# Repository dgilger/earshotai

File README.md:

# Earshot

A self-hosted, DIY AI note taker. Earshot records conversations, turns them into text on hardware you own,
and keeps the audio away from third-party clouds.

> **Recording consent:** laws differ by country and state. Some places require every person's consent
> before you record a conversation. Check the law where you use Earshot.

## Parts of the project

| Folder | What it is | Status |
|---|---|---|
| [`android/`](android/README.md) | Android app: record, transcribe on the phone with speaker labels, save each transcript as a `.txt` file in a folder you choose. Audio is deleted after. | Works; APK built by GitHub Actions |
| [`server/`](server/) | Python service: receives audio over HTTP, transcribes with faster-whisper, optional summary (Claude API or any OpenAI-compatible local LLM). | Desk prototype |
| [`firmware/`](firmware/) | PlatformIO firmware for an ESP32-S3 board (ES8311 codec mic, touchscreen): record and upload to the server. | Desk prototype |
| [`hardware/`](hardware/SPEC.md) | Wearable rev A: nRF52840 board in KiCad 9, with JLCPCB fab files, plus a sealed 3D-printable enclosure (CadQuery). | Designed, not built |

## Quick start

**Android app.** Open the **Actions** tab, select the latest **Android APK** run, download `earshot-apk`,
and install the APK on an arm64 Android 10+ phone. See [`android/README.md`](android/README.md).

**Server.**
```sh
cd server
uv venv --python 3.12 .venv
uv pip install --python .venv/bin/python -r requirements.txt
cp .env.example .env        # choose a summary backend, or SUMMARY_BACKEND=none
.venv/bin/python -u earshot_server.py   # listens on port 8000
```

**Self-hosted server.** Install, web portal, remote access and setup details are in
[`server/README.md`](server/README.md).

**Firmware.** Copy `firmware/include/secrets.example.h` to `secrets.h`, fill in your Wi-Fi and server URL,
then run `pio run -t upload` from `firmware/`.

## Privacy

- The Android app transcribes on the phone. No audio or text leaves the phone except through the folder you pick.
- The server runs on your own machine. Summaries go to the Claude API only if you select that backend;
  select `local` or `none` to keep everything on your network.
- Secrets (`secrets.h`, `.env`) are gitignored. Do not commit them.

## License

MIT, see [LICENSE](LICENSE). Some files keep their own licenses:
- `android/app/src/main/java/com/k2fsa/sherpa/onnx/`: from [sherpa-onnx](https://github.com/k2-fsa/sherpa-onnx), Apache-2.0.
- `android/app/src/main/res/font/`: Silkscreen and Space Mono, SIL Open Font License (see `android/licenses/`).
- `hardware/earshot-revA/lib/`: footprints and 3D models imported from LCSC/EasyEDA with easyeda2kicad.

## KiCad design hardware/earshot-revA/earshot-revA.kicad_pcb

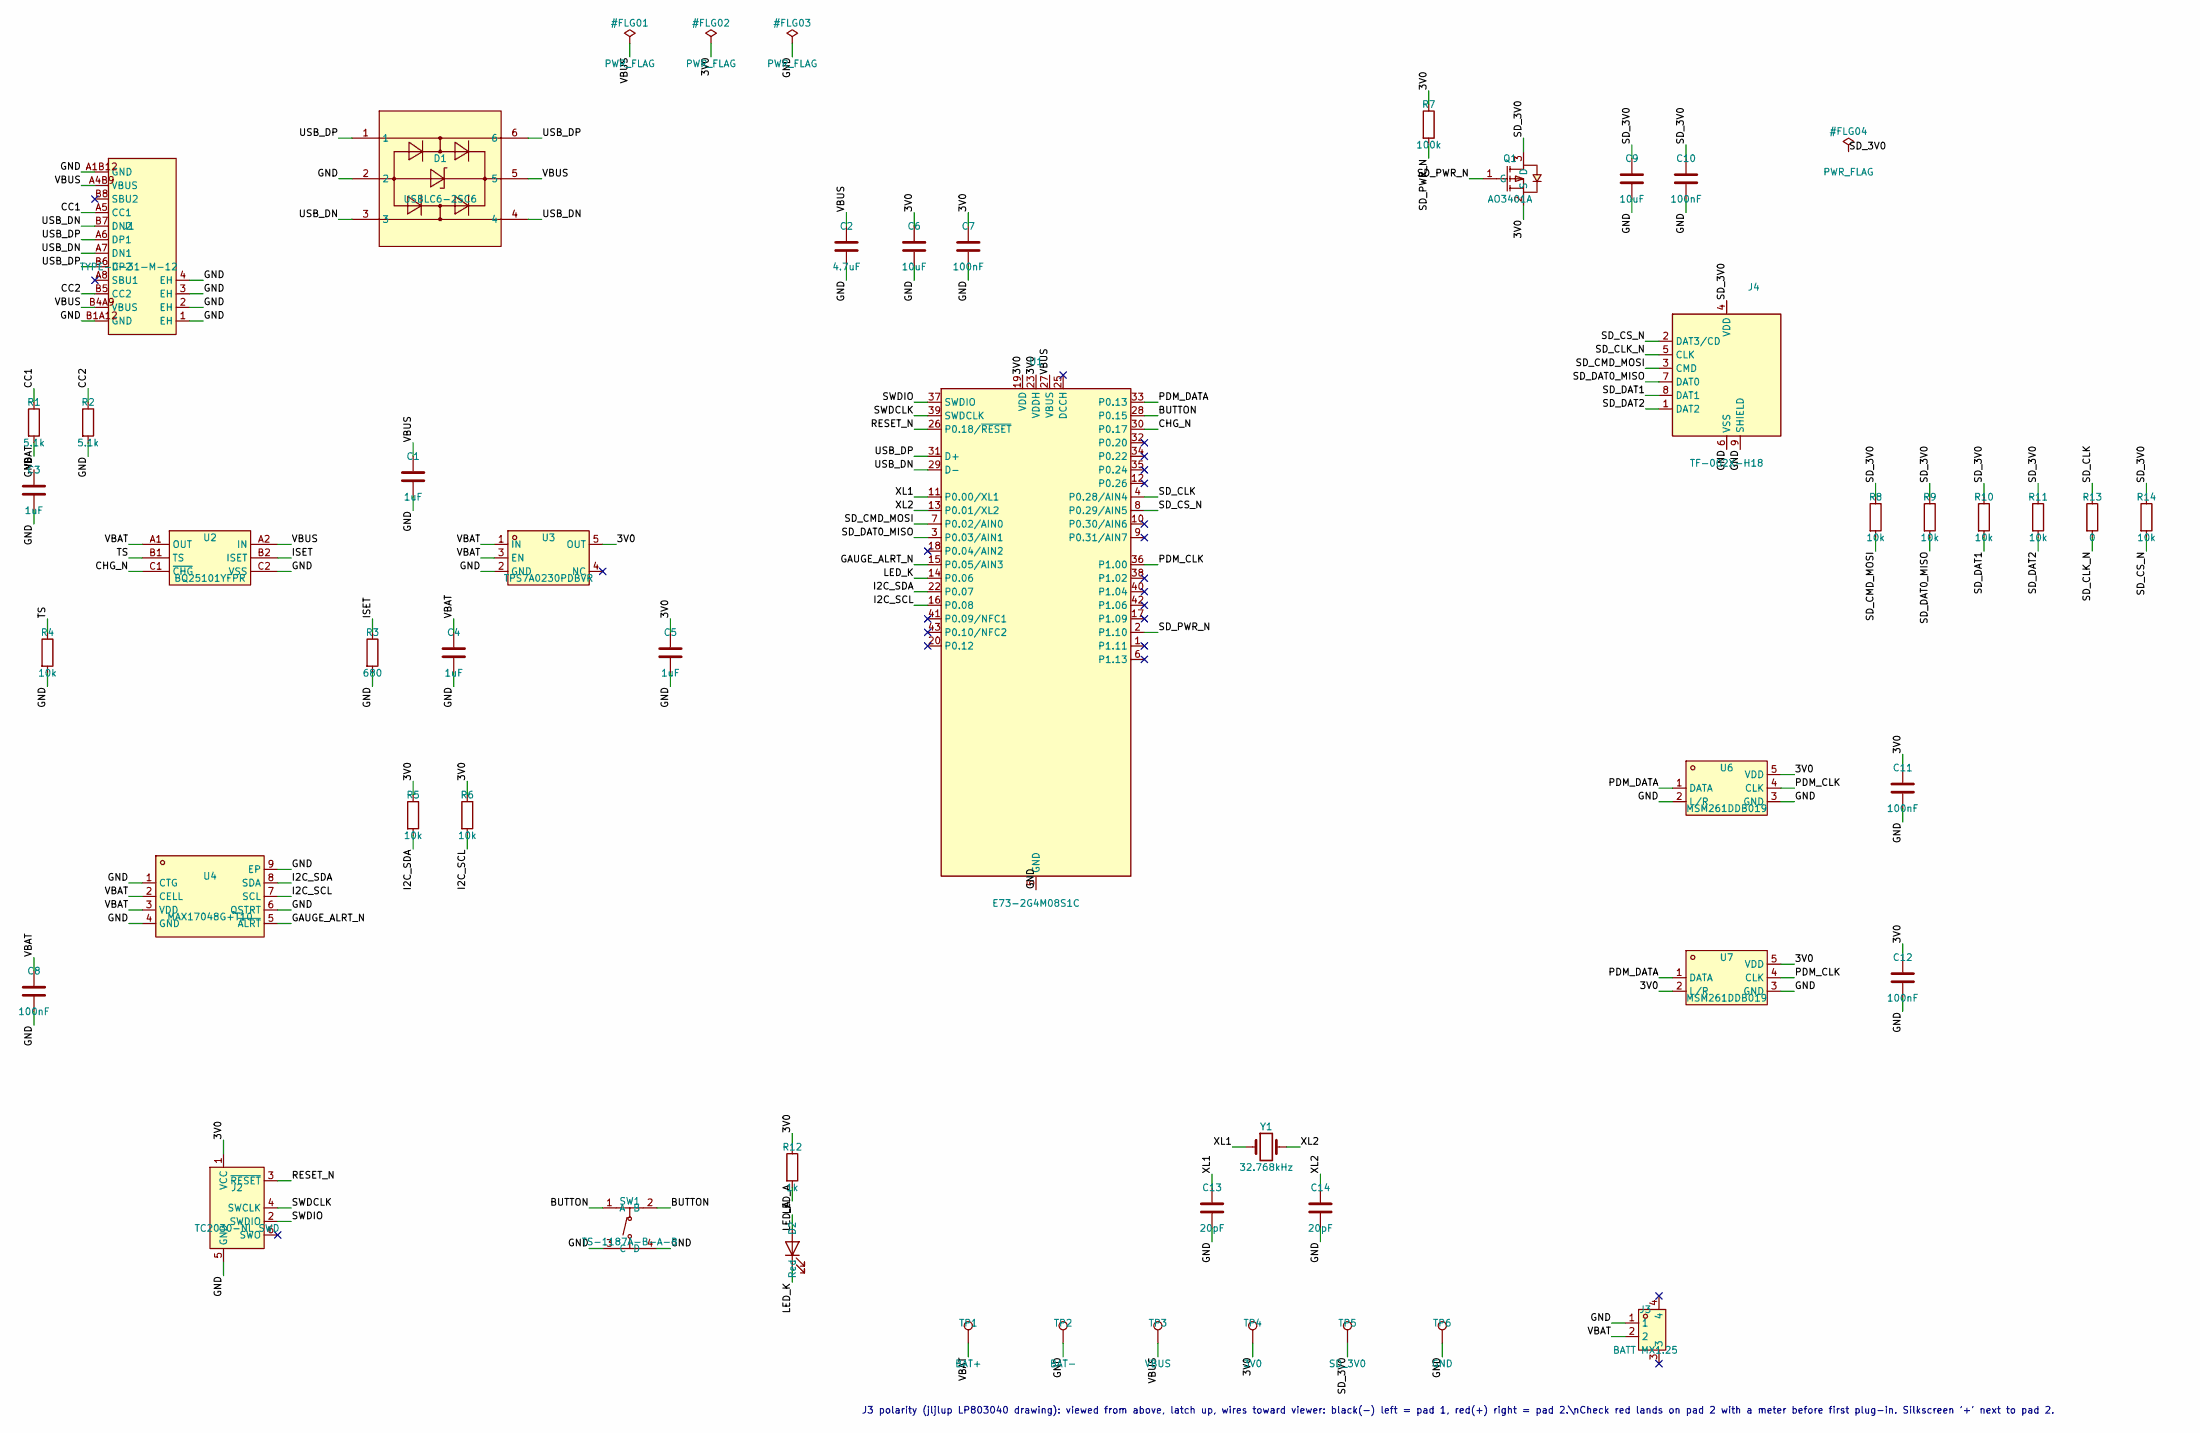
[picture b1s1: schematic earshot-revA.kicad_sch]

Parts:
C1, C3, C4, C5: 1uF; C_0402_1005Metric; LCSC Part C52923
C2: 4.7uF; C_0603_1608Metric; LCSC Part C19666
C6, C9: 10uF; C_0603_1608Metric; LCSC Part C19702
C7, C8, C10, C11, C12: 100nF; C_0402_1005Metric; LCSC Part C1525
C13, C14: 20pF; C_0402_1005Metric; LCSC Part C1554
D1: USBLC6-2SC6; SOT-23-6_L2.9-W1.6-P0.95-LS2.8-BL
D2: Red; LED_0603_1608Metric; LCSC C2286
J1: TYPE-C-31-M-12; USB-C_SMD-TYPE-C-31-M-12_1
J2: TC2030-NL SWD; Tag-Connect_TC2030-IDC-NL_2x03_P1.27mm_Vertical
J3: BATT MX1.25; CONN-SMD_2P-P1.25-2
J4: TF-002X-H18; microSD_Hinged_SOFNG_TF-002X-H18; MPN TF-002X-H18; LCSC Part C125814
Q1: AO3401A; SOT-23_L2.9-W1.3-P1.90-LS2.4-BR
R1, R2: 5.1k; R_0402_1005Metric; LCSC Part C25905
R3: 680; R_0402_1005Metric; LCSC Part C25130
R4, R5, R6, R8, R9, R10, R11, R14: 10k; R_0402_1005Metric; LCSC Part C60490
R7: 100k; R_0402_1005Metric; LCSC Part C25741
R12: 1k; R_0402_1005Metric; LCSC Part C11702
R13: 0; R_0402_1005Metric; LCSC Part C17168
SW1: TS-1187A-B-A-B; SW-SMD_4P-L5.1-W5.1-P3.70-LS6.5-TL_H1.5
TP1: BAT+; TestPoint_Pad_2.0x2.0mm
TP2: BAT-; TestPoint_Pad_2.0x2.0mm
TP3: VBUS; TestPoint_Pad_D1.0mm
TP4: 3V0; TestPoint_Pad_D1.0mm
TP5: SD_3V0; TestPoint_Pad_D1.0mm
TP6: GND; TestPoint_Pad_D1.0mm
U1: E73-2G4M08S1C; MPN E73-2G4M08S1C; LCSC Part C356849
U2: BQ25101YFPR; DSBGA-6_L0.9-W1.6-R2-C3-P0.40-BL
U3: TPS7A0230PDBVR; SOT-23-5_L2.9-W1.6-P0.95-LS2.8-BR
U4: MAX17048G+T10; TDFN-8_L2.0-W2.0-P0.50-BL-EP1.2
U6, U7: MSM261DDB019; RHLGA-5L_L3.5-W2.7-P0.82-MSM261DDB019
Y1: 32.768kHz; Crystal_SMD_3215-2Pin_3.2x1.5mm; LCSC C32346

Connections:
/3V0: C5.1, C6.1, C7.1, C11.1, C12.1, J2.1 (VCC), Q1.2 (S), R5.1, R6.1, R7.1, R12.1, TP4.1, U1.19 (VDD), U1.23 (VDDH), U3.5 (OUT), U6.5 (VDD), U7.2 (L/R), U7.5 (VDD)
/BUTTON: SW1.1 (A), SW1.2 (B), U1.28 (P0.15)
/CC1: J1.A5 (CC1), R1.1
/CC2: J1.B5 (CC2), R2.1
/CHG_N: U1.30 (P0.17), U2.C1 (~CHG)
/GAUGE_ALRT_N: U1.15 (P0.05/AIN3), U4.5 (~ALRT)
/GND: C1.2, C2.2, C3.2, C4.2, C5.2, C6.2, C7.2, C8.2, C9.2, C10.2, C11.2, C12.2, C13.2, C14.2, D1.2, J1.1 (EH), J1.2 (EH), J1.3 (EH), J1.4 (EH), J1.A1B12 (GND), J1.B1A12 (GND), J2.5 (GND), J3.1, J4.6 (VSS), J4.9 (SHIELD), R1.2, R2.2, R3.2, R4.2, SW1.3 (C), SW1.4 (D), TP2.1, TP6.1, U1.5 (GND), U1.21 (GND), U1.24 (GND), U2.C2 (VSS), U3.2 (GND), U4.1 (CTG), U4.4 (GND), U4.6 (QSTRT), U4.9 (EP), U6.2 (L/R), U6.3 (GND), U7.3 (GND)
/I2C_SCL: R6.2, U1.16 (P0.08), U4.7 (SCL)
/I2C_SDA: R5.2, U1.22 (P0.07), U4.8 (SDA)
/ISET: R3.1, U2.B2 (ISET)
/LED_A: D2.2 (A), R12.2
/LED_K: D2.1 (K), U1.14 (P0.06)
/PDM_CLK: U1.36 (P1.00), U6.4 (CLK), U7.4 (CLK)
/PDM_DATA: U1.33 (P0.13), U6.1 (DATA), U7.1 (DATA)
/RESET_N: J2.3 (~RESET), U1.26 (P0.18/~RESET)
/SD_3V0: C9.1, C10.1, J4.4 (VDD), Q1.3 (D), R8.1, R9.1, R10.1, R11.1, R14.1, TP5.1
/SD_CLK: R13.1, U1.4 (P0.28/AIN4)
/SD_CLK_N: J4.5 (CLK), R13.2
/SD_CMD_MOSI: J4.3 (CMD), R8.2, U1.7 (P0.02/AIN0)
/SD_CS_N: J4.2 (DAT3/CD), R14.2, U1.8 (P0.29/AIN5)
/SD_DAT0_MISO: J4.7 (DAT0), R9.2, U1.3 (P0.03/AIN1)
/SD_DAT1: J4.8 (DAT1), R10.2
/SD_DAT2: J4.1 (DAT2), R11.2
/SD_PWR_N: Q1.1 (G), R7.2, U1.2 (P1.10)
/SWDCLK: J2.4 (SWCLK), U1.39 (SWDCLK)
/SWDIO: J2.2 (SWDIO), U1.37 (SWDIO)
/TS: R4.1, U2.B1 (TS)
/USB_DN: D1.3, D1.4, J1.A7 (DN1), J1.B7 (DN2), U1.29 (D-)
/USB_DP: D1.1, D1.6, J1.A6 (DP1), J1.B6 (DP2), U1.31 (D+)
/VBAT: C3.1, C4.1, C8.1, J3.2, TP1.1, U2.A1 (OUT), U3.1 (IN), U3.3 (EN), U4.2 (CELL), U4.3 (VDD)
/VBUS: C1.1, C2.1, D1.5, J1.A4B9 (VBUS), J1.B4A9 (VBUS), TP3.1, U1.27 (VBUS), U2.A2 (IN)
/XL1: C13.1, U1.11 (P0.00/XL1), Y1.1
/XL2: C14.1, U1.13 (P0.01/XL2), Y1.2

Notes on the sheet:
J3 polarity (jljlup LP803040 drawing): viewed from above, latch up, wires toward viewer: black(-) left = pad 1, red(+) right = pad 2.\nCheck red lands on pad 2 with a meter before first plug-in. Silkscreen '+' next to pad 2.

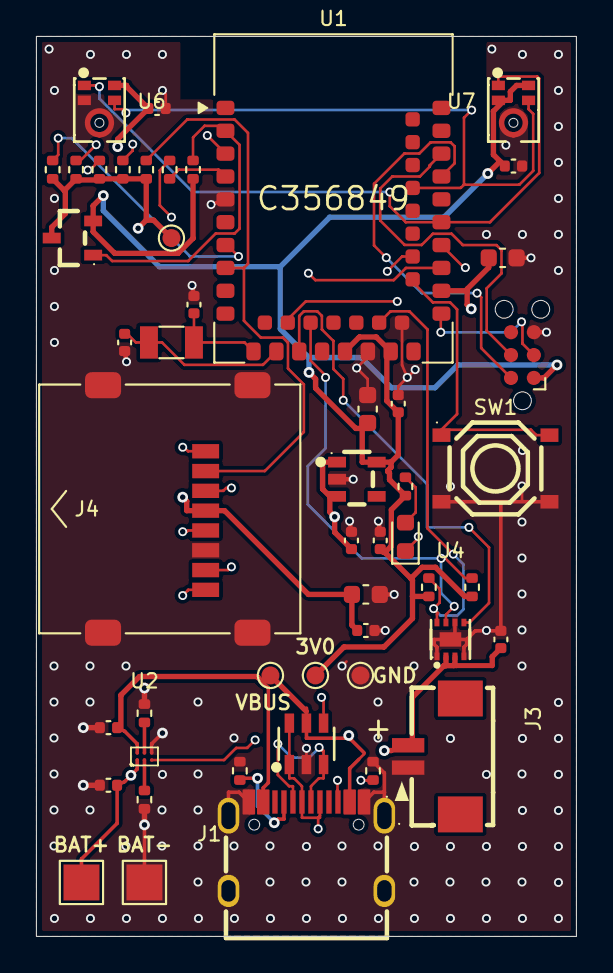
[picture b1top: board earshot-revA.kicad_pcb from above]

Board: 4 copper layers, 30.0 x 50.0 mm, 50 parts (1 on the bottom side), 33 nets.

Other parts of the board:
LOGO1: Earshot_Logo_10mm

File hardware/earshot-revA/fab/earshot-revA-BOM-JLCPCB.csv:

Comment,Designator,Footprint,LCSC Part #
1uF,"C1,C3,C4,C5",C_0402_1005Metric,C52923
4.7uF,C2,C_0603_1608Metric,C19666
10uF,"C6,C9",C_0603_1608Metric,C19702
100nF,"C7,C8,C10,C11,C12",C_0402_1005Metric,C1525
20pF,"C13,C14",C_0402_1005Metric,C1554
USBLC6-2SC6,D1,SOT-23-6_L2.9-W1.6-P0.95-LS2.8-BL,C7519
Red,D2,LED_0603_1608Metric,C2286
TYPE-C-31-M-12,J1,USB-C_SMD-TYPE-C-31-M-12_1,C165948
BATT MX1.25,J3,CONN-SMD_2P-P1.25-2,C53477378
TF-002X-H18,J4,microSD_Hinged_SOFNG_TF-002X-H18,C125814
AO3401A,Q1,SOT-23_L2.9-W1.3-P1.90-LS2.4-BR,C15127
5.1k,"R1,R2",R_0402_1005Metric,C25905
680,R3,R_0402_1005Metric,C25130
10k,"R4,R5,R6,R8,R9,R10,R11,R14",R_0402_1005Metric,C60490
100k,R7,R_0402_1005Metric,C25741
1k,R12,R_0402_1005Metric,C11702
0,R13,R_0402_1005Metric,C17168
TS-1187A-B-A-B,SW1,SW-SMD_4P-L5.1-W5.1-P3.70-LS6.5-TL_H1.5,C318884
E73-2G4M08S1C,U1,E73-2G4M08S1C,C356849
BQ25101YFPR,U2,DSBGA-6_L0.9-W1.6-R2-C3-P0.40-BL,C478468
TPS7A0230PDBVR,U3,SOT-23-5_L2.9-W1.6-P0.95-LS2.8-BR,C3747031
MAX17048G+T10,U4,TDFN-8_L2.0-W2.0-P0.50-BL-EP1.2,C2682616
MSM261DDB019,"U6,U7",RHLGA-5L_L3.5-W2.7-P0.82-MSM261DDB019,C51928210
32.768kHz,Y1,Crystal_SMD_3215-2Pin_3.2x1.5mm,C32346

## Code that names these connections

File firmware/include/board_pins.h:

// ES3C28P pin map. Source: official schematic + IO allocation table
// (https://www.lcdwiki.com/2.8inch_ESP32-S3_Display), checked 2026-11-01.
#pragma once

// Shared I2C bus: ES8311 codec (0x18) + FT6336G touch (0x38)
#define PIN_I2C_SDA     16
#define PIN_I2C_SCL     15
#define I2C_ADDR_ES8311 0x18
#define I2C_ADDR_FT6336 0x38

// ES8311 I2S. Net names on the schematic are from the codec's side:
// codec ASDOUT (mic/ADC data) -> GPIO6, GPIO8 -> codec DSDIN (DAC/speaker data).
#define PIN_I2S_MCLK    4
#define PIN_I2S_BCLK    5
#define PIN_I2S_WS      7
#define PIN_I2S_DIN     6   // ESP32 input  <- mic
#define PIN_I2S_DOUT    8   // ESP32 output -> speaker
#define PIN_AMP_EN      1   // FM8002E shutdown, low = amp on

// ILI9341V LCD, 4-wire SPI. Reset is tied to the ESP32 EN line (no GPIO).
#define PIN_LCD_SCLK    12
#define PIN_LCD_MOSI    11
#define PIN_LCD_MISO    13
#define PIN_LCD_CS      10
#define PIN_LCD_DC      46
#define PIN_LCD_BL      45  // high = backlight on

// FT6336G capacitive touch
#define PIN_TOUCH_INT   17  // low on touch
#define PIN_TOUCH_RST   18  // low = reset

// microSD, SDIO 4-bit
#define PIN_SD_CLK      38
#define PIN_SD_CMD      40
#define PIN_SD_D0       39
#define PIN_SD_D1       41
#define PIN_SD_D2       48
#define PIN_SD_D3       47

#define PIN_BAT_ADC     9
#define PIN_WS2812      42  // RGB LED (framework already defines PIN_RGB_LED)
#define PIN_BOOT_BTN    0

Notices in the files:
parts and their libraries:
Pad numbers and functions from the Ebyte E73-2G4M08S1C user manual; pad centres match hlord2000/nordic-lib-kicad (CERN-OHL-P) and the SnapEDA land pattern.
